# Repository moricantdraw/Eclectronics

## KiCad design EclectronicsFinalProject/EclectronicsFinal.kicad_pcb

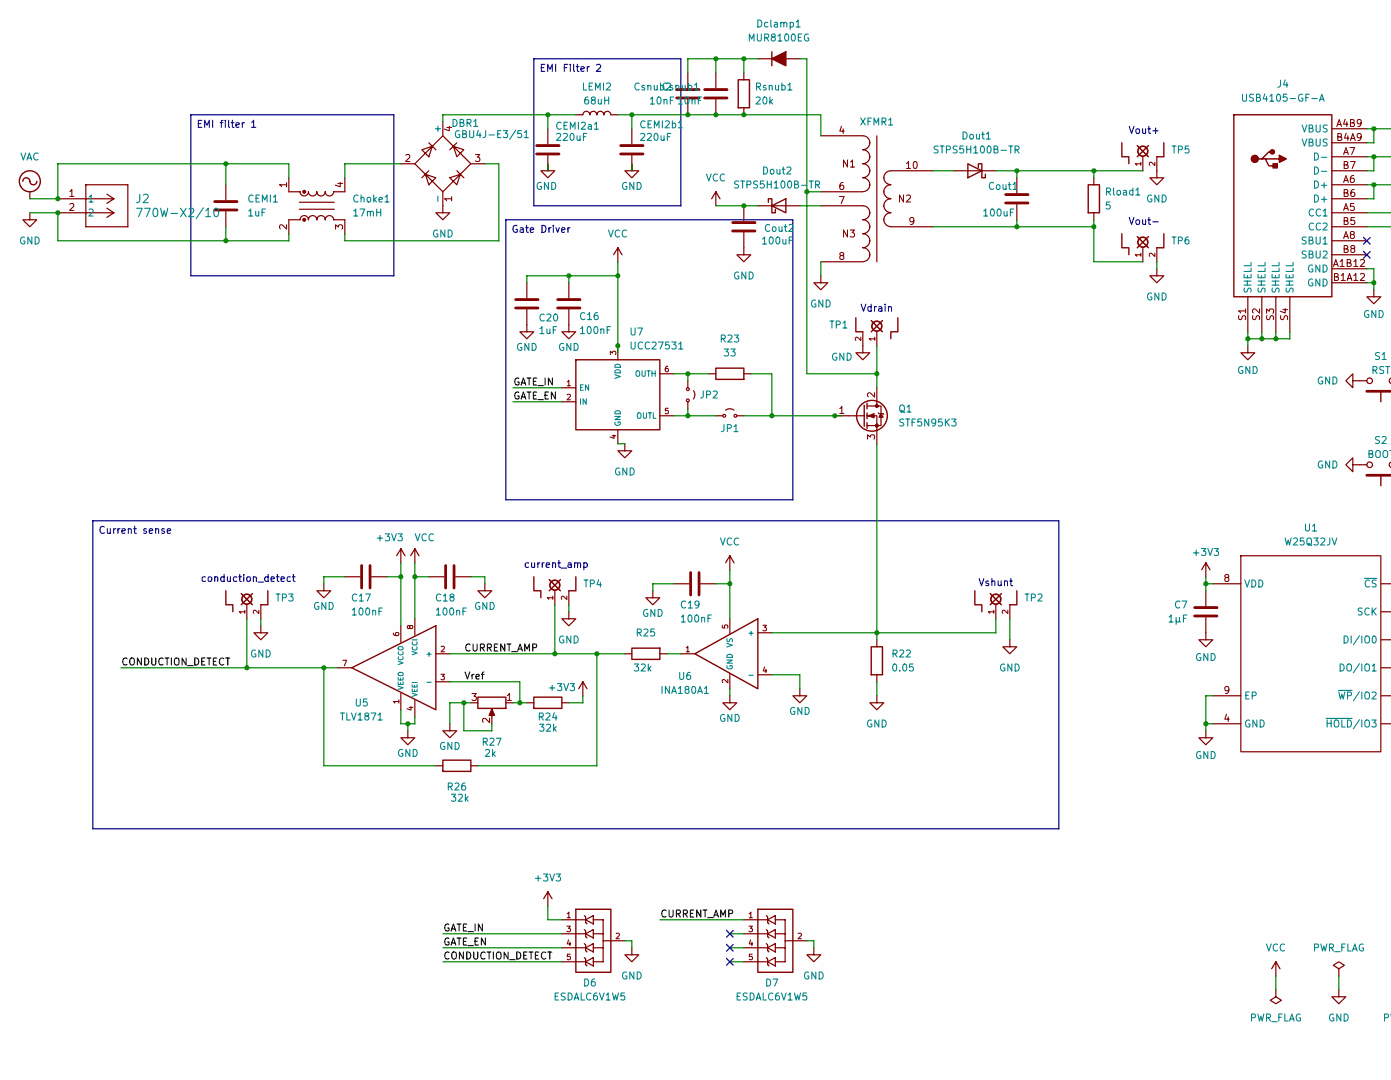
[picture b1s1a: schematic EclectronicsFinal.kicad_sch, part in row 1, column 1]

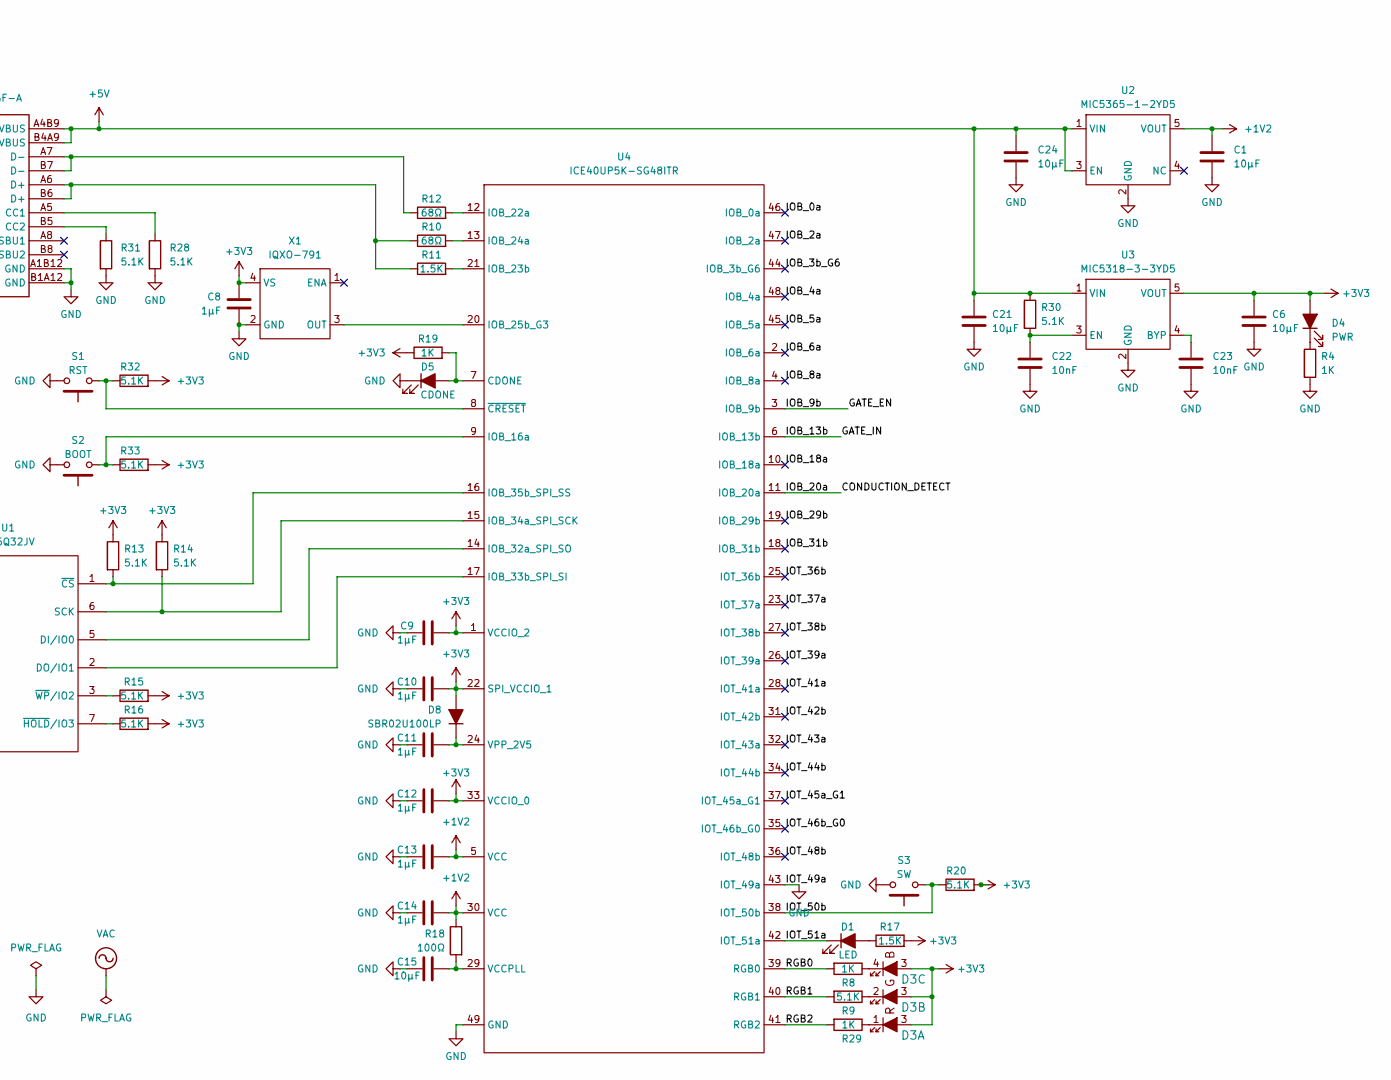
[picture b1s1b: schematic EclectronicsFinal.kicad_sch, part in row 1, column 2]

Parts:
C1, C6, C15, C21, C24: 10µF; C_0603_1608Metric
C7, C8, C9, C10, C11, C12, C13, C14: 1µF; C_0603_1608Metric
C16, C17, C18, C19: 100nF; C_0603_1608Metric
C20: 1uF; C_0603_1608Metric
C22, C23: 10nF; C_0603_1608Metric
CEMI1: 1uF; CAPRR1000W60L1260T920H1390
CEMI2a1, CEMI2b1: 220uF; CAP_RADIAL_M50_18Dx50L_CHC
Choke1: 17mH; WE-CMBNC_M_7448030417
Cout1, Cout2: 100uF; CAP_6.5 X 12.5 X 18
Csnub1, Csnub2: 10nF; CAP_6.5 X 12.5 X 18
D1: LED; D_0805_2012Metric
D3: IN-S85TATRGB_ALT; LED_Kingbright_APHBM2012_2x1.25mm
D4: PWR; D_0805_2012Metric
D5: CDONE; D_0805_2012Metric
D6, D7: ESDALC6V1W5; SOT-353_SC-70-5; MPN ESDALC6V1W5
D8: SBR02U100LP; D_0603_1608Metric
DBR1: GBU4J-E3/51; Diode_Bridge_Vishay_GBU
Dclamp1: MUR8100EG; TO-220-2_Vertical
Dout1, Dout2: STPS5H100B-TR; DPAK_STM
J2: 770W-X2/10; CONN2_770W-X2&slash_10_QLK
J4: USB4105-GF-A
JP1, JP2: Jumper_2_Small_Open; SolderJumper-2_Open_Hooks0.8x1.8mm
LEMI2: 68uH; IND_BOURNS_SRR1260
Q1: STF5N95K3; TO-220-3_Vertical; MPN FDP61N20
R4, R8, R19, R29: 1K; R_0603_1608Metric
R9, R13, R14, R15, R16, R20, R28, R30, R31, R32, R33: 5.1K; R_0603_1608Metric
R10, R12: 68Ω; R_0603_1608Metric
R11, R17: 1.5K; R_0603_1608Metric
R18: 100Ω; R_0603_1608Metric
R22: 0.05; R_2512_6332Metric
R23: 33; R_0603_1608Metric
R24, R25, R26: 32k; R_0603_1608Metric
R27: 2k; R_0603_1608Metric
Rload1: 5; STA_KAL50_STP
Rsnub1: 20k; R_2512_6332Metric
S1: RST; B3U-1000P
S2: BOOT; B3U-1000P
S3: SW; B3U-1000P
TP1, TP2, TP3, TP4, TP5, TP6: TP_SCOPE
U1: W25Q32JV; WDFN-8-1EP_6x5mm_P1.27mm_EP3.4x4mm
U2: MIC5365-1-2YD5; TSOT-23-5
U3: MIC5318-3-3YD5; TSOT-23-5
U4: ICE40UP5K-SG48ITR; QFN-48-1EP_7x7mm_P0.5mm_EP5.3x5.3mm
U5: TLV1871; TSOT-23-8; MPN TLV1871DDFR
U6: INA180A1; INA180A1IDBVR; MPN INA180A1IDBVR
U7: UCC27531; SOT-23-6; MPN UCC27531DBVR
X1: IQXO-791; Oscillator_SMD_SeikoEpson_SG210-4Pin_2.5x2.0mm
XFMR1: 750817436; T_Wurth_WE-OLSTM-EE16_7_5_750817436; Part Number 750343068

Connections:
+1V2: C1.1, C13.2, C14.2, R18.1, U2.5 (VOUT), U4.5 (VCC), U4.30 (VCC)
+3V3: C6.1, C7.1, C8.1, C9.2, C10.2, C12.2, C17.2, D3.3, D4.2 (A), D6.1, D8.2 (A), R13.1, R14.1, R15.2, R16.2, R17.2, R19.1, R20.2, R24.1, R32.2, R33.2, U1.8 (VDD), U3.5 (VOUT), U4.1 (VCCIO_2), U4.22 (SPI_VCCIO_1), U4.33 (VCCIO_0), U5.6 (VCCO), X1.4 (VS)
+5V: C21.1, C24.1, J4.A4B9 (VBUS), J4.B4A9 (VBUS), R30.1, U2.1 (VIN), U2.3 (EN), U3.1 (VIN)
/CONDUCTION_DETECT: D6.5, R26.2, TP3.1, U4.11 (IOB_20a), U5.7
/CURRENT_AMP: D7.1, R25.1, R26.1, TP4.1, U5.2 (+)
/GATE_EN: D6.4, U4.3 (IOB_9b), U7.2 (IN)
/GATE_IN: D6.3, U4.6 (IOB_13b), U7.1 (EN)
/IOB_0a: U4.46 (IOB_0a)
/IOB_2a: U4.47 (IOB_2a)
/IOB_3b_G6: U4.44 (IOB_3b_G6)
/IOB_4a: U4.48 (IOB_4a)
/IOB_5a: U4.45 (IOB_5a)
/IOB_6a: U4.2 (IOB_6a)
/IOB_8a: U4.4 (IOB_8a)
/IOB_18a: U4.10 (IOB_18a)
/IOB_29b: U4.19 (IOB_29b)
/IOB_31b: U4.18 (IOB_31b)
/IOT_36b: U4.25 (IOT_36b)
/IOT_37a: U4.23 (IOT_37a)
/IOT_38b: U4.27 (IOT_38b)
/IOT_39a: U4.26 (IOT_39a)
/IOT_41a: U4.28 (IOT_41a)
/IOT_42b: U4.31 (IOT_42b)
/IOT_43a: U4.32 (IOT_43a)
/IOT_44b: U4.34 (IOT_44b)
/IOT_45a_G1: U4.37 (IOT_45a_G1)
/IOT_46b_G0: U4.35 (IOT_46b_G0)
/IOT_48b: U4.36 (IOT_48b)
/IOT_50b: R20.1, S3.1, U4.38 (IOT_50b)
/IOT_51a: D1.1 (K), U4.42 (IOT_51a)
/RGB0: R8.2, U4.39 (RGB0)
/RGB1: R9.2, U4.40 (RGB1)
/RGB2: R29.2, U4.41 (RGB2)
/Vref: R24.2, R27.1, U5.3 (-)
GND: C1.2, C6.2, C7.2, C8.2, C9.1, C10.1, C11.1, C12.1, C13.1, C14.1, C15.1, C16.2, C17.1, C18.2, C19.1, C20.2, C21.2, C22.2, C23.2, C24.2, CEMI1.2, CEMI2a1.2, CEMI2b1.2, Choke1.2, Cout2.2, D5.1 (K), D6.2, D7.2, DBR1.1 (-), J2.2, J4.A1B12 (GND), J4.B1A12 (GND), J4.S1 (SHELL), J4.S2 (SHELL), J4.S3 (SHELL), J4.S4 (SHELL), R4.2, R22.2, R27.2, R27.3, R28.2, R31.2, S1.2, S2.2, S3.2, TP1.2, TP2.2, TP3.2, TP4.2, TP5.2, TP6.2, U1.4 (GND), U1.9 (EP), U2.2 (GND), U3.2 (GND), U4.43 (IOT_49a), U4.49 (GND), U5.1 (VEEO), U5.4 (VEEI), U6.2 (GND), U6.4 (-), U7.4 (GND), X1.2 (GND), XFMR1.8
unnamed: CEMI2b1.1, Csnub1.2, Csnub2.2, LEMI2.2, Rsnub1.2, XFMR1.4
unnamed: Choke1.3, DBR1.3
unnamed: Choke1.4, DBR1.2
unnamed: Cout1.2, Rload1.2, TP6.1, XFMR1.9
unnamed: D1.2 (A), R17.1
unnamed: D3.1, R29.1
unnamed: D3.2, R9.1
unnamed: D3.4, R8.1
unnamed: D4.1 (K), R4.1
unnamed: D5.2 (A), R19.2, U4.7 (CDONE)
unnamed: C11.2, D8.1 (K), U4.24 (VPP_2V5)
unnamed: CEMI2a1.1, DBR1.4 (+), LEMI2.1
unnamed: Dclamp1.2 (A), Q1.2 (D), TP1.1, XFMR1.6
unnamed: Csnub1.1, Csnub2.1, Dclamp1.1 (K), Rsnub1.1
unnamed: Dout1.2 (A), XFMR1.10
unnamed: Cout1.1, Dout1.1 (K), Rload1.1, TP5.1
unnamed: Dout2.2 (A), XFMR1.7
unnamed: J4.A5 (CC1), R28.1
unnamed: J4.B5 (CC2), R31.1
unnamed: J4.A6 (D+), J4.B6 (D+), R10.1, R11.1
unnamed: J4.A7 (D-), J4.B7 (D-), R12.1
unnamed: JP1.1 (A), JP2.2 (B), U7.5 (OUTL)
unnamed: JP1.2 (B), Q1.1 (G), R23.2
unnamed: JP2.1 (A), R23.1, U7.6 (OUTH)
unnamed: Q1.3 (S), R22.1, TP2.1, U6.3 (+)
unnamed: R25.2, U6.1
unnamed: U1.5 (DI/IO0), U4.14 (IOB_32a_SPI_SO)
unnamed: U1.2 (DO/IO1), U4.17 (IOB_33b_SPI_SI)
unnamed: R14.2, U1.6 (SCK), U4.15 (IOB_34a_SPI_SCK)
unnamed: R13.2, U1.1 (~CS), U4.16 (IOB_35b_SPI_SS)
unnamed: R16.1, U1.7 (~HOLD/IO3)
unnamed: R15.1, U1.3 (~WP/IO2)
unnamed: C23.1, U3.4 (BYP)
unnamed: C22.1, R30.2, U3.3 (EN)
unnamed: R33.1, S2.1, U4.9 (IOB_16a)
unnamed: R12.2, U4.12 (IOB_22a)
unnamed: R11.2, U4.21 (IOB_23b)
unnamed: R10.2, U4.13 (IOB_24a)
unnamed: U4.20 (IOB_25b_G3), X1.3 (OUT)
unnamed: C15.2, R18.2, U4.29 (VCCPLL)
unnamed: R32.1, S1.1, U4.8 (~CRESET)
VAC: CEMI1.1, Choke1.1, J2.1
VCC: C16.1, C18.1, C19.2, C20.1, Cout2.1, Dout2.1 (K), U5.8 (VCCI), U6.5 (VS), U7.3 (VDD)

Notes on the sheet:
Vout-
Vout+
Vdrain
conduction_detect
Vshunt
current_amp
EMI Filter 2
EMI filter 1
Current sense
Gate Driver

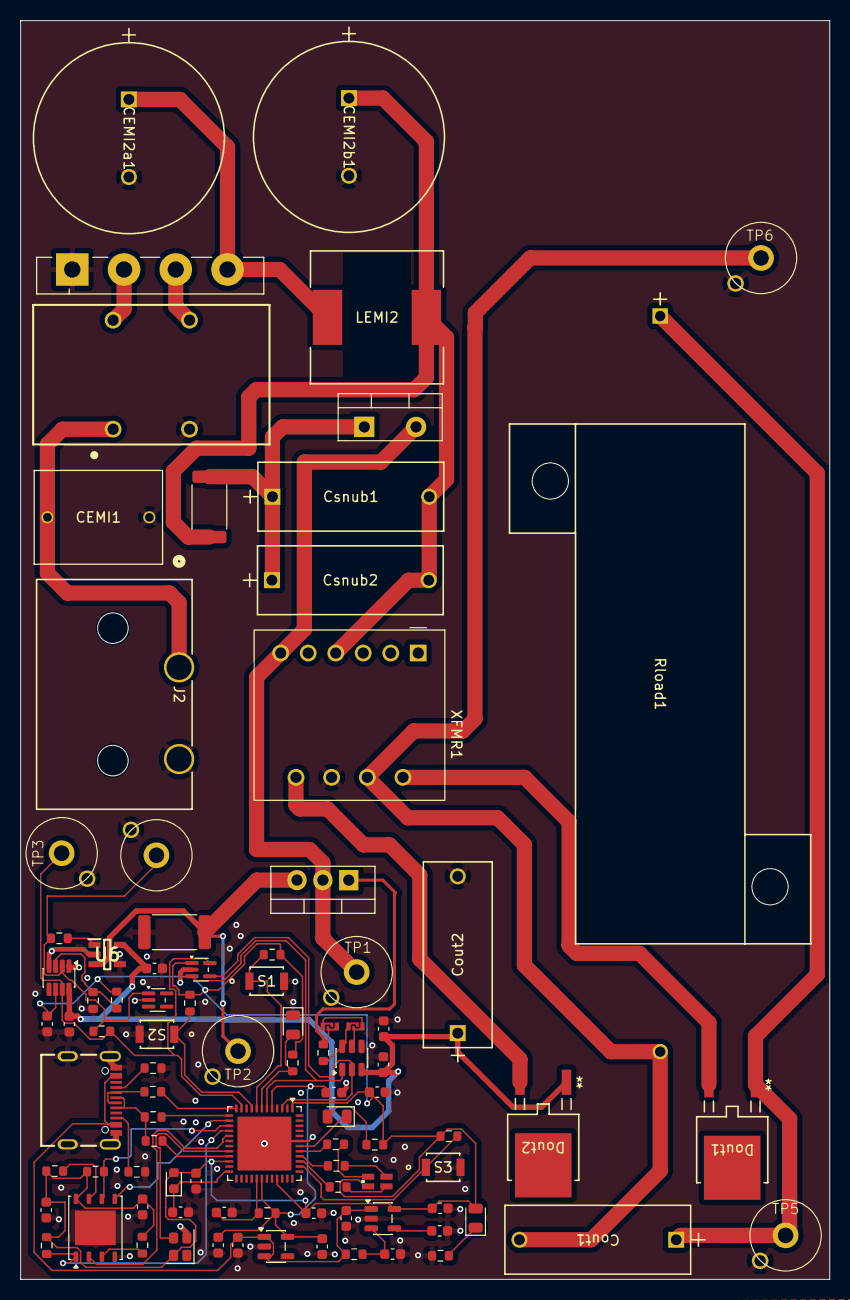
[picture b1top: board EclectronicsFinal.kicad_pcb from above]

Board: 2 copper layers, 79.4 x 123.6 mm, 91 parts (0 on the bottom side), 57 nets.

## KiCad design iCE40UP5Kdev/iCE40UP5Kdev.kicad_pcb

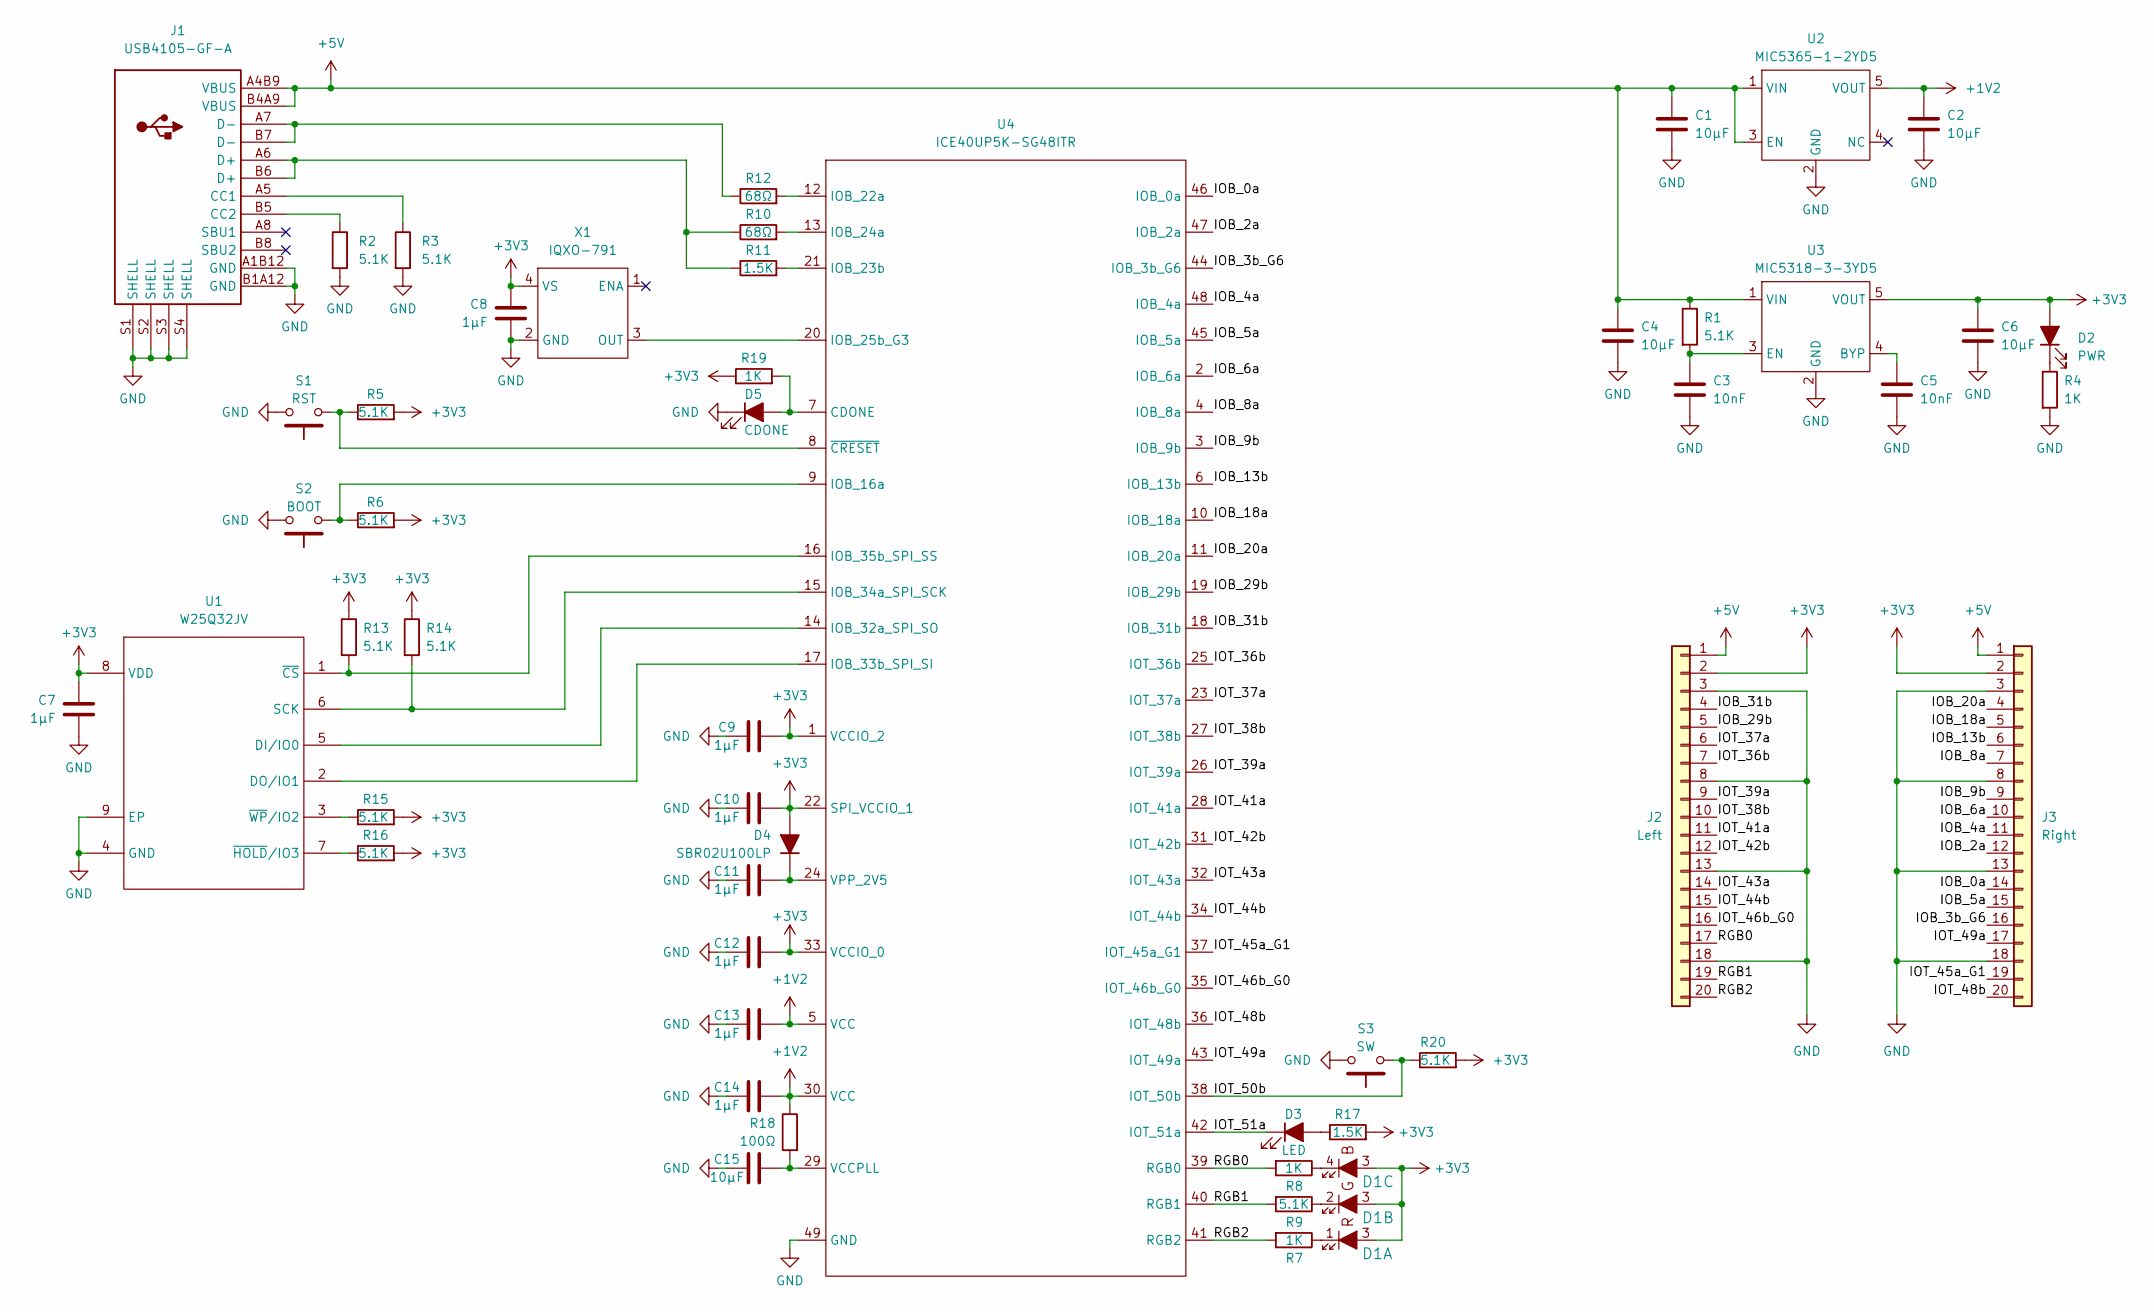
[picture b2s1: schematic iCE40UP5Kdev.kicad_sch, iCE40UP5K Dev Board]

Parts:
C1, C2, C4, C6, C15: 10µF; C_0603_1608Metric
C3, C5: 10nF; C_0603_1608Metric
C7, C8, C9, C10, C11, C12, C13, C14: 1µF; C_0603_1608Metric
D1: IN-S85TATRGB_ALT; LED_Kingbright_APHBM2012_2x1.25mm
D2: PWR; D_0805_2012Metric
D3: LED; D_0805_2012Metric
D4: SBR02U100LP; D_0603_1608Metric
D5: CDONE; D_0805_2012Metric
J1: USB4105-GF-A
J2: Left; PinHeader_1x20_P2.54mm_Vertical
J3: Right; PinHeader_1x20_P2.54mm_Vertical
R1, R2, R3, R5, R6, R9, R13, R14, R15, R16, R20: 5.1K; R_0603_1608Metric
R4, R7, R8, R19: 1K; R_0603_1608Metric
R10, R12: 68Ω; R_0603_1608Metric
R11, R17: 1.5K; R_0603_1608Metric
R18: 100Ω; R_0603_1608Metric
S1: RST; B3U-1000P
S2: BOOT; B3U-1000P
S3: SW; B3U-1000P
U1: W25Q32JV; WDFN-8-1EP_6x5mm_P1.27mm_EP3.4x4mm
U2: MIC5365-1-2YD5; TSOT-23-5
U3: MIC5318-3-3YD5; TSOT-23-5
U4: ICE40UP5K-SG48ITR; QFN-48-1EP_7x7mm_P0.5mm_EP5.3x5.3mm
X1: IQXO-791; Oscillator_SMD_SeikoEpson_SG210-4Pin_2.5x2.0mm

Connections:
+1V2: C2.1, C13.2, C14.2, R18.1, U2.5 (VOUT), U4.5 (VCC), U4.30 (VCC)
+3V3: C6.1, C7.1, C8.1, C9.2, C10.2, C12.2, D1.3, D2.2 (A), D4.2 (A), J2.2, J3.2, R5.2, R6.2, R13.1, R14.1, R15.2, R16.2, R17.2, R19.1, R20.2, U1.8 (VDD), U3.5 (VOUT), U4.1 (VCCIO_2), U4.22 (SPI_VCCIO_1), U4.33 (VCCIO_0), X1.4 (VS)
+5V: C1.1, C4.1, J1.A4B9 (VBUS), J1.B4A9 (VBUS), J2.1, J3.1, R1.1, U2.1 (VIN), U2.3 (EN), U3.1 (VIN)
/IOB_0a: J3.14, U4.46 (IOB_0a)
/IOB_2a: J3.12, U4.47 (IOB_2a)
/IOB_3b_G6: J3.16, U4.44 (IOB_3b_G6)
/IOB_4a: J3.11, U4.48 (IOB_4a)
/IOB_5a: J3.15, U4.45 (IOB_5a)
/IOB_6a: J3.10, U4.2 (IOB_6a)
/IOB_8a: J3.7, U4.4 (IOB_8a)
/IOB_9b: J3.9, U4.3 (IOB_9b)
/IOB_13b: J3.6, U4.6 (IOB_13b)
/IOB_18a: J3.5, U4.10 (IOB_18a)
/IOB_20a: J3.4, U4.11 (IOB_20a)
/IOB_29b: J2.5, U4.19 (IOB_29b)
/IOB_31b: J2.4, U4.18 (IOB_31b)
/IOT_36b: J2.7, U4.25 (IOT_36b)
/IOT_37a: J2.6, U4.23 (IOT_37a)
/IOT_38b: J2.10, U4.27 (IOT_38b)
/IOT_39a: J2.9, U4.26 (IOT_39a)
/IOT_41a: J2.11, U4.28 (IOT_41a)
/IOT_42b: J2.12, U4.31 (IOT_42b)
/IOT_43a: J2.14, U4.32 (IOT_43a)
/IOT_44b: J2.15, U4.34 (IOT_44b)
/IOT_45a_G1: J3.19, U4.37 (IOT_45a_G1)
/IOT_46b_G0: J2.16, U4.35 (IOT_46b_G0)
/IOT_48b: J3.20, U4.36 (IOT_48b)
/IOT_49a: J3.17, U4.43 (IOT_49a)
/IOT_50b: R20.1, S3.1, U4.38 (IOT_50b)
/IOT_51a: D3.1 (K), U4.42 (IOT_51a)
/RGB0: J2.17, R8.2, U4.39 (RGB0)
/RGB1: J2.19, R9.2, U4.40 (RGB1)
/RGB2: J2.20, R7.2, U4.41 (RGB2)
GND: C1.2, C2.2, C3.2, C4.2, C5.2, C6.2, C7.2, C8.2, C9.1, C10.1, C11.1, C12.1, C13.1, C14.1, C15.1, D5.1 (K), J1.A1B12 (GND), J1.B1A12 (GND), J1.S1 (SHELL), J1.S2 (SHELL), J1.S3 (SHELL), J1.S4 (SHELL), J2.3, J2.8, J2.13, J2.18, J3.3, J3.8, J3.13, J3.18, R2.2, R3.2, R4.2, S1.2, S2.2, S3.2, U1.4 (GND), U1.9 (EP), U2.2 (GND), U3.2 (GND), U4.49 (GND), X1.2 (GND)
unnamed: D1.1, R7.1
unnamed: D1.2, R9.1
unnamed: D1.4, R8.1
unnamed: D2.1 (K), R4.1
unnamed: D3.2 (A), R17.1
unnamed: C11.2, D4.1 (K), U4.24 (VPP_2V5)
unnamed: D5.2 (A), R19.2, U4.7 (CDONE)
unnamed: J1.A5 (CC1), R3.1
unnamed: J1.B5 (CC2), R2.1
unnamed: J1.A6 (D+), J1.B6 (D+), R10.1, R11.1
unnamed: J1.A7 (D-), J1.B7 (D-), R12.1
unnamed: U1.5 (DI/IO0), U4.14 (IOB_32a_SPI_SO)
unnamed: U1.2 (DO/IO1), U4.17 (IOB_33b_SPI_SI)
unnamed: R14.2, U1.6 (SCK), U4.15 (IOB_34a_SPI_SCK)
unnamed: R13.2, U1.1 (~CS), U4.16 (IOB_35b_SPI_SS)
unnamed: R16.1, U1.7 (~HOLD/IO3)
unnamed: R15.1, U1.3 (~WP/IO2)
unnamed: C5.1, U3.4 (BYP)
unnamed: C3.1, R1.2, U3.3 (EN)
unnamed: R6.1, S2.1, U4.9 (IOB_16a)
unnamed: R12.2, U4.12 (IOB_22a)
unnamed: R11.2, U4.21 (IOB_23b)
unnamed: R10.2, U4.13 (IOB_24a)
unnamed: U4.20 (IOB_25b_G3), X1.3 (OUT)
unnamed: C15.2, R18.2, U4.29 (VCCPLL)
unnamed: R5.1, S1.1, U4.8 (~CRESET)

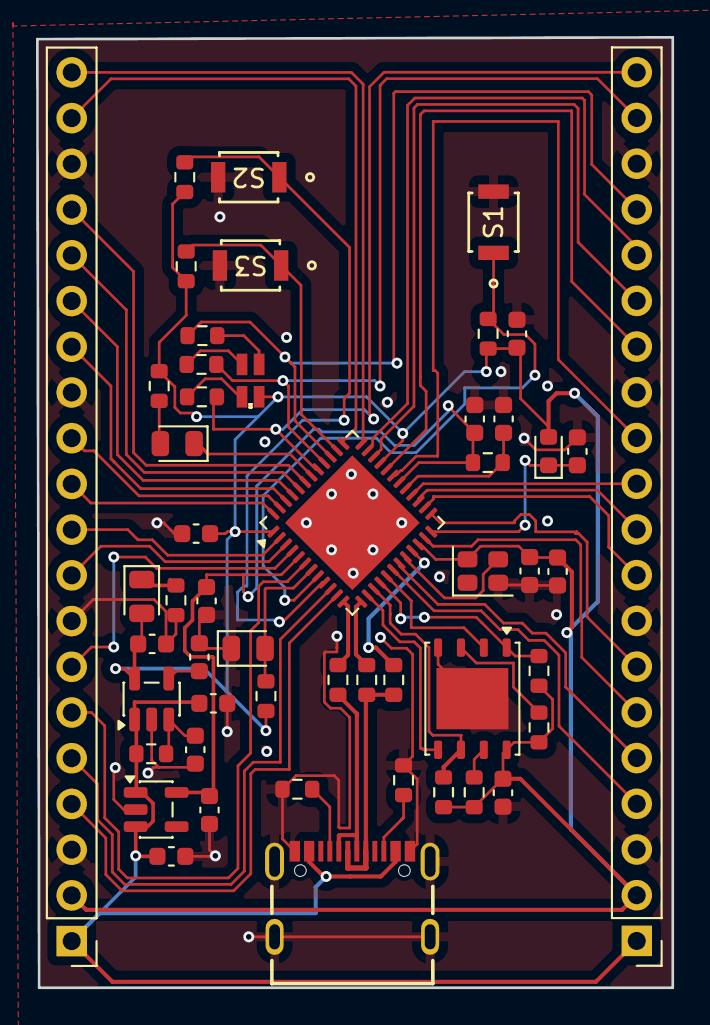
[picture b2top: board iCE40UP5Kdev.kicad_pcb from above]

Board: 2 copper layers, 35.3 x 52.8 mm, 51 parts (0 on the bottom side), 60 nets.

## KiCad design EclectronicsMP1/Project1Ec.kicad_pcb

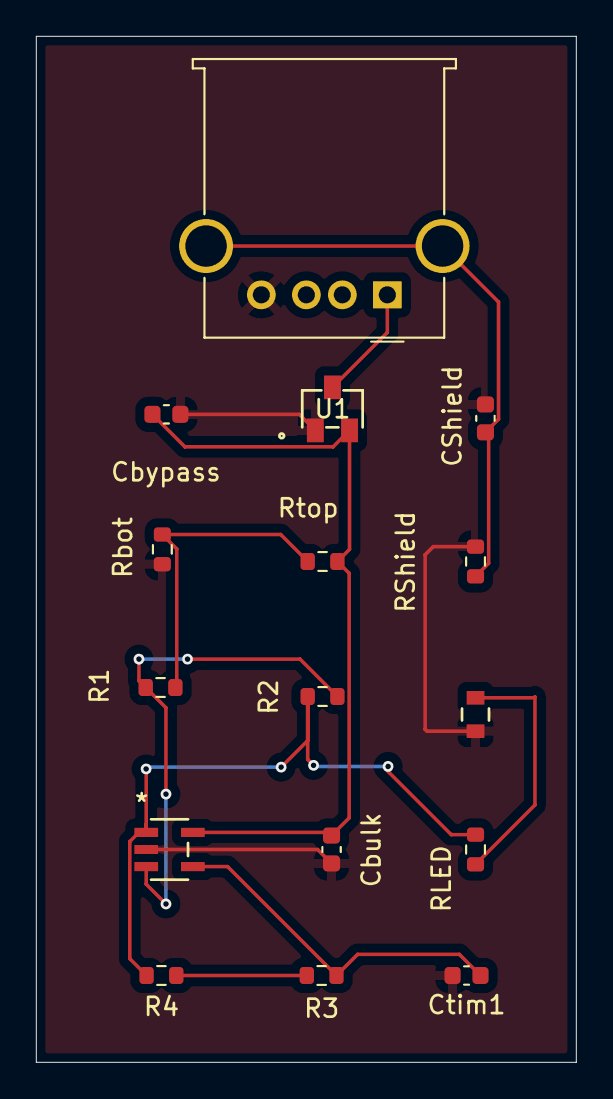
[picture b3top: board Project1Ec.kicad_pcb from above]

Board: 4 copper layers, 30.0 x 57.0 mm, 16 parts (0 on the bottom side), 10 nets.

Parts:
CShield: 0.01u; C_0603_1608Metric
Cbulk: 1u; C_0603_1608Metric
Cbypass: 0.01u; C_0603_1608Metric
Ctim1: 10u; C_0603_1608Metric
J1: USB_A; USB_A_Molex_67643_Horizontal
LED1: LED; LED_LTST-C171_LTO
R1: 200k; R_0603_1608Metric
R2: 470k; R_0603_1608Metric
R3: 40.02k; R_0603_1608Metric
R4: 15.8k; R_0603_1608Metric
RLED: 158k; R_0603_1608Metric
RShield: 1Meg; R_0603_1608Metric
Rbot: 100k; R_0603_1608Metric
Rtop: 301k; R_0603_1608Metric
U1: Linear Reg; SOT-23A_MC_MCH
U2: OPAMP; SOT-23-5_MC_MCH

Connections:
+3.3V: Cbulk.1, Cbypass.1, Rtop.1, U1.2 (VOUT), U2.5 (VDD)
+5V: J1.1 (VBUS), U1.3 (VIN)
GND: CShield.2, Cbulk.2, Cbypass.2, Ctim1.1, J1.4 (GND), LED1.1, RShield.2, Rbot.2, U1.1 (GND), U2.2 (VSS)
unnamed: CShield.1, J1.5 (Shield), RShield.1
unnamed: LED1.2, RLED.1
unnamed: R1.2, Rbot.1, Rtop.2
unnamed: R3.1, R4.2
unnamed: R1.1, R2.2, U2.3 (VIN+)
unnamed: Ctim1.2, R3.2, U2.4 (VIN-)
unnamed: R2.1, R4.1, RLED.2, U2.1 (VOUT)

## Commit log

2026-03-09 folder 1
2026-03-09 Create MP3
2026-03-09 Rename Eclectronics.pretty.zip to MP3Part1/Eclectronics.pretty.zip
2026-03-09 organized MP3 files
2026-03-09 deleted extra MP3 files
2026-03-11 Add files via upload
    Edited version
2026-03-11 reorganized loose files for MP3
2026-04-18 footprints and symbols
2026-04-18 final files
2026-04-18 enclose final project files in shared folder
2026-04-18 remove duplicate files
2026-04-20 revision
2026-04-22 traces fixed
